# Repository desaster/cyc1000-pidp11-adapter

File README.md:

# pidp11 ↔ cyc1000 adapter

This is an adapter board to connect the
[CYC1000](https://shop.trenz-electronic.de/en/Products/Trenz-Electronic/CYC1000-Intel-Cyclone-10/)
FPGA module to the
[PiDP-11, PDP-11/70 front panel replica](https://obsolescence.wixsite.com/obsolescence/pidp-11).

It is intended to be used with [PDP2011](http://pdp2011.sytse.net/), an FPGA
implementation of the PDP-11 by Sytse van Slooten.

In addition to routing the necessary pins to the panel, the board also
includes some components for use with the PDP2011:

* Micro-SDCard connector
* USB-UART bridge using the [CP2102](https://www.silabs.com/products/interface/usb-bridges/classic-usb-bridges/device.cp2102)
* Pin headers for connecting to [PMODNIC100](https://store.digilentinc.com/pmod-nic100-network-interface-controller/)

## Design considerations

* Power input from PiDP-11 header via VIN
* CYC1000 is placed underneath the adapter for clearance with the back panel
* CP2102 is bus-powered, and will not power the rest of the circuit
* The packages are chosen based on what I happen to have in my shelves

## TODO

* Actually test if the design works
* Replace CP2102 footprint with something easier to solder
* Integrate ENC424J600 to the board

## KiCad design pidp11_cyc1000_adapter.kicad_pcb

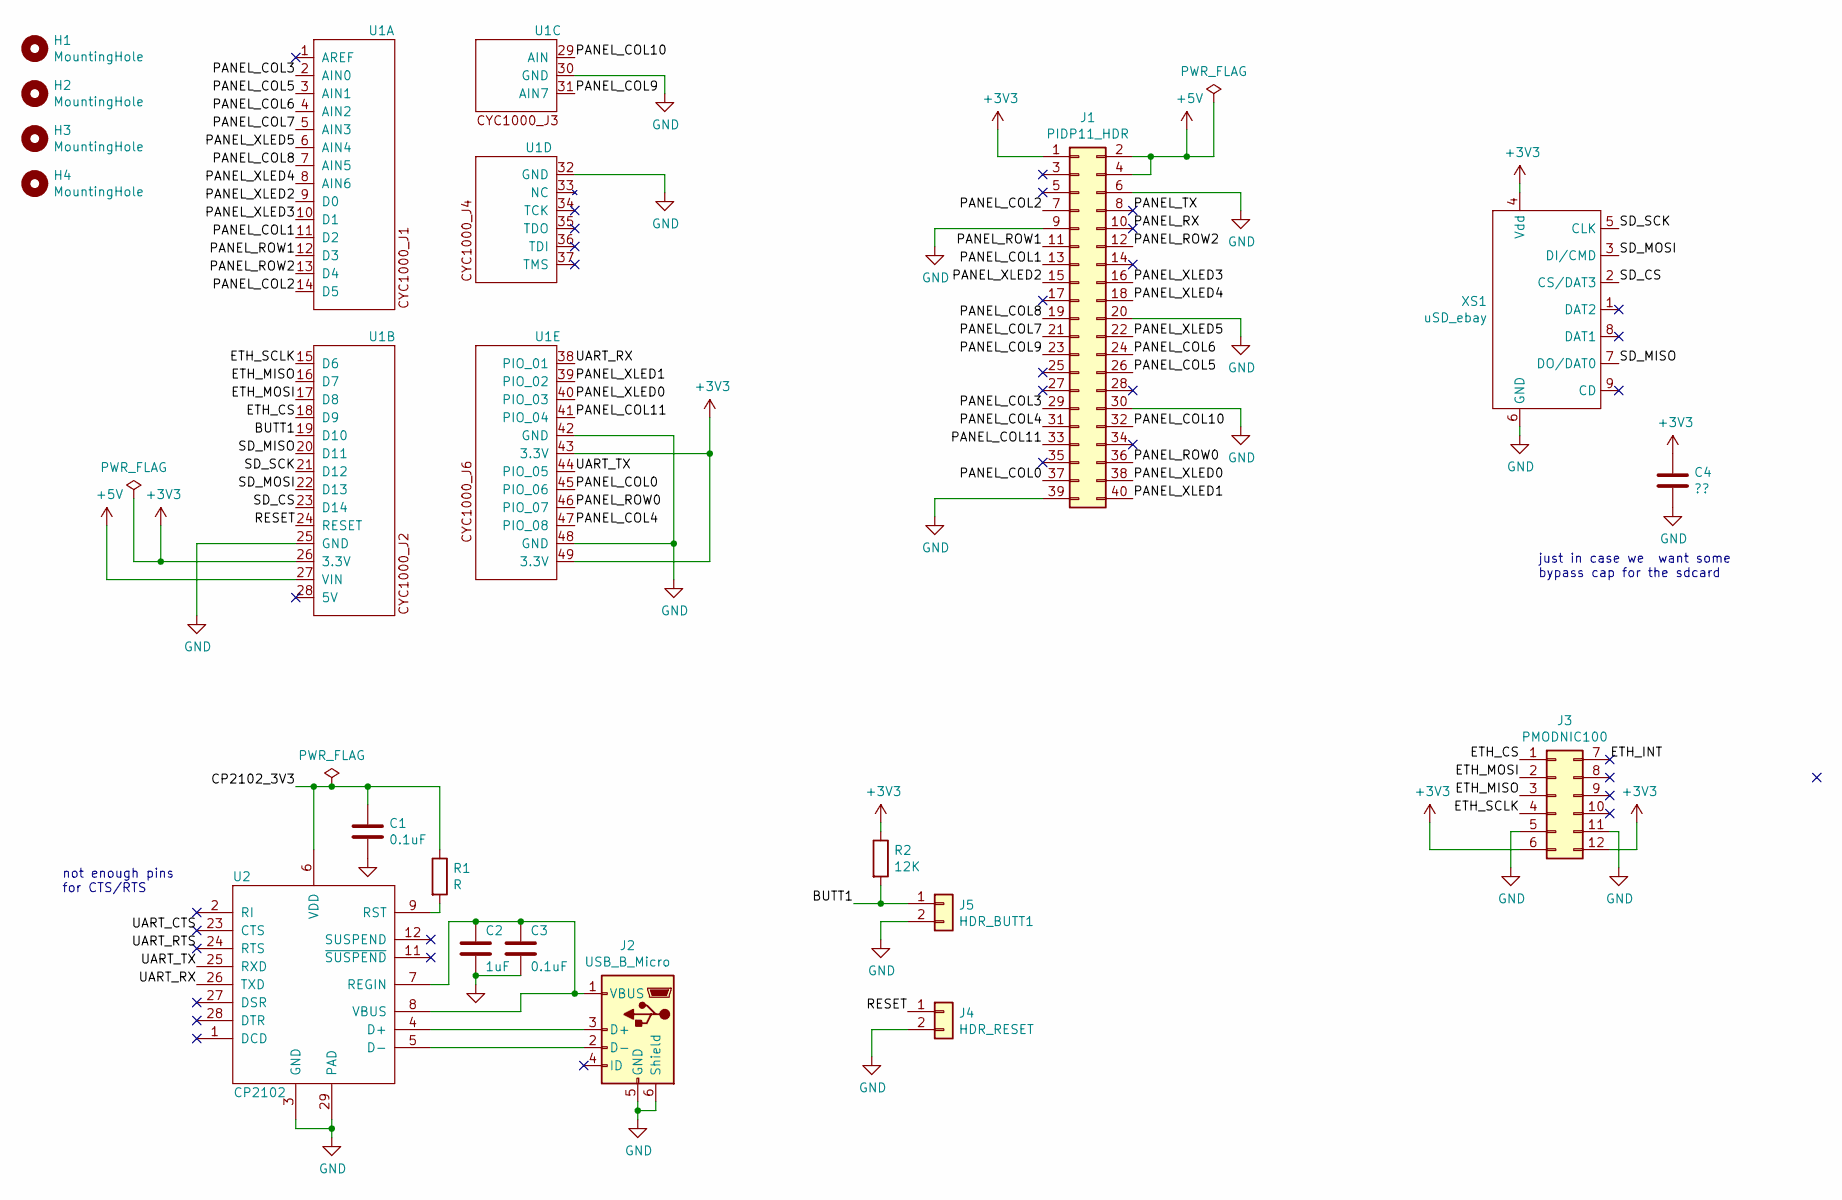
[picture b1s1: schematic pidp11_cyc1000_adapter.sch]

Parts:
C1: 0.1uF; C_0805_2012Metric
C2: 1uF; C_0805_2012Metric_Pad1.15x1.40mm_HandSolder
C3: 0.1uF; C_0805_2012Metric_Pad1.15x1.40mm_HandSolder
C4: ??; C_0805_2012Metric_Pad1.15x1.40mm_HandSolder
H1, H2, H3, H4: MountingHole; MountingHole_RasPI
J1: PIDP11_HDR; PinHeader_2x20_P2.54mm_Vertical
J2: USB_B_Micro; USB_Mini-B_Lumberg_2486_01_Horizontal
J3: PMODNIC100; PMOD_2x06
J4: HDR_RESET; PinHeader_1x02_P2.54mm_Horizontal
J5: HDR_BUTT1; PinHeader_1x02_P2.54mm_Horizontal
R1: R; R_0805_2012Metric_Pad1.15x1.40mm_HandSolder
R2: 12K; R_0805_2012Metric_Pad1.15x1.40mm_HandSolder
U1: CYC1000
U2: CP2102; QFN-28-1EP_5x5mm_Pitch0.5mm
XS1: uSD_ebay; Conn_uSDcard

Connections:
+3V3: C4.1, J1.1, J3.6, J3.12, R2.1, U1.26 (3.3V), U1.43 (3.3V), U1.49 (3.3V), XS1.4 (Vdd)
+5V: J1.2, J1.4, U1.27 (VIN)
/BUTT1: J5.1, R2.2, U1.19 (D10)
/CP2102_3V3: C1.1, R1.1, U2.6 (VDD)
/ETH_CS: J3.1, U1.18 (D9)
/ETH_INT: J3.7
/ETH_MISO: J3.3, U1.16 (D7)
/ETH_MOSI: J3.2, U1.17 (D8)
/ETH_SCLK: J3.4, U1.15 (D6)
/PANEL_COL0: J1.37, U1.45 (PIO_06)
/PANEL_COL1: J1.13, U1.11 (D2)
/PANEL_COL2: J1.7, U1.14 (D5)
/PANEL_COL3: J1.29, U1.2 (AIN0)
/PANEL_COL4: J1.31, U1.47 (PIO_08)
/PANEL_COL5: J1.26, U1.3 (AIN1)
/PANEL_COL6: J1.24, U1.4 (AIN2)
/PANEL_COL7: J1.21, U1.5 (AIN3)
/PANEL_COL8: J1.19, U1.7 (AIN5)
/PANEL_COL9: J1.23, U1.31 (AIN7)
/PANEL_COL10: J1.32, U1.29 (AIN)
/PANEL_COL11: J1.33, U1.41 (PIO_04)
/PANEL_ROW0: J1.36, U1.46 (PIO_07)
/PANEL_ROW1: J1.11, U1.12 (D3)
/PANEL_ROW2: J1.12, U1.13 (D4)
/PANEL_RX: J1.10
/PANEL_TX: J1.8
/PANEL_XLED0: J1.38, U1.40 (PIO_03)
/PANEL_XLED1: J1.40, U1.39 (PIO_02)
/PANEL_XLED2: J1.15, U1.9 (D0)
/PANEL_XLED3: J1.16, U1.10 (D1)
/PANEL_XLED4: J1.18, U1.8 (AIN6)
/PANEL_XLED5: J1.22, U1.6 (AIN4)
/RESET: J4.1, U1.24 (RESET)
/SD_CS: U1.23 (D14), XS1.2 (CS/DAT3)
/SD_MISO: U1.20 (D11), XS1.7 (DO/DAT0)
/SD_MOSI: U1.22 (D13), XS1.3 (DI/CMD)
/SD_SCK: U1.21 (D12), XS1.5 (CLK)
/UART_CTS: U2.23 (CTS)
/UART_RTS: U2.24 (RTS)
/UART_RX: U1.38 (PIO_01), U2.26 (TXD)
/UART_TX: U1.44 (PIO_05), U2.25 (RXD)
GND: C1.2, C2.2, C3.2, C4.2, J1.6, J1.9, J1.20, J1.30, J1.39, J2.5 (GND), J2.6 (Shield), J3.5, J3.11, J4.2, J5.2, U1.25 (GND), U1.30 (GND), U1.32 (GND), U1.42 (GND), U1.48 (GND), U2.3 (GND), U2.29 (PAD), XS1.6 (GND)
unnamed: C2.1, C3.1, J2.1 (VBUS), U2.7 (REGIN), U2.8 (VBUS)
unnamed: J2.2 (D-), U2.5 (D-)
unnamed: J2.3 (D+), U2.4 (D+)
unnamed: R1.2, U2.9 (RST)

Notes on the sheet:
just in case we want some bypass cap for the sdcard
not enough pins for CTS/RTS

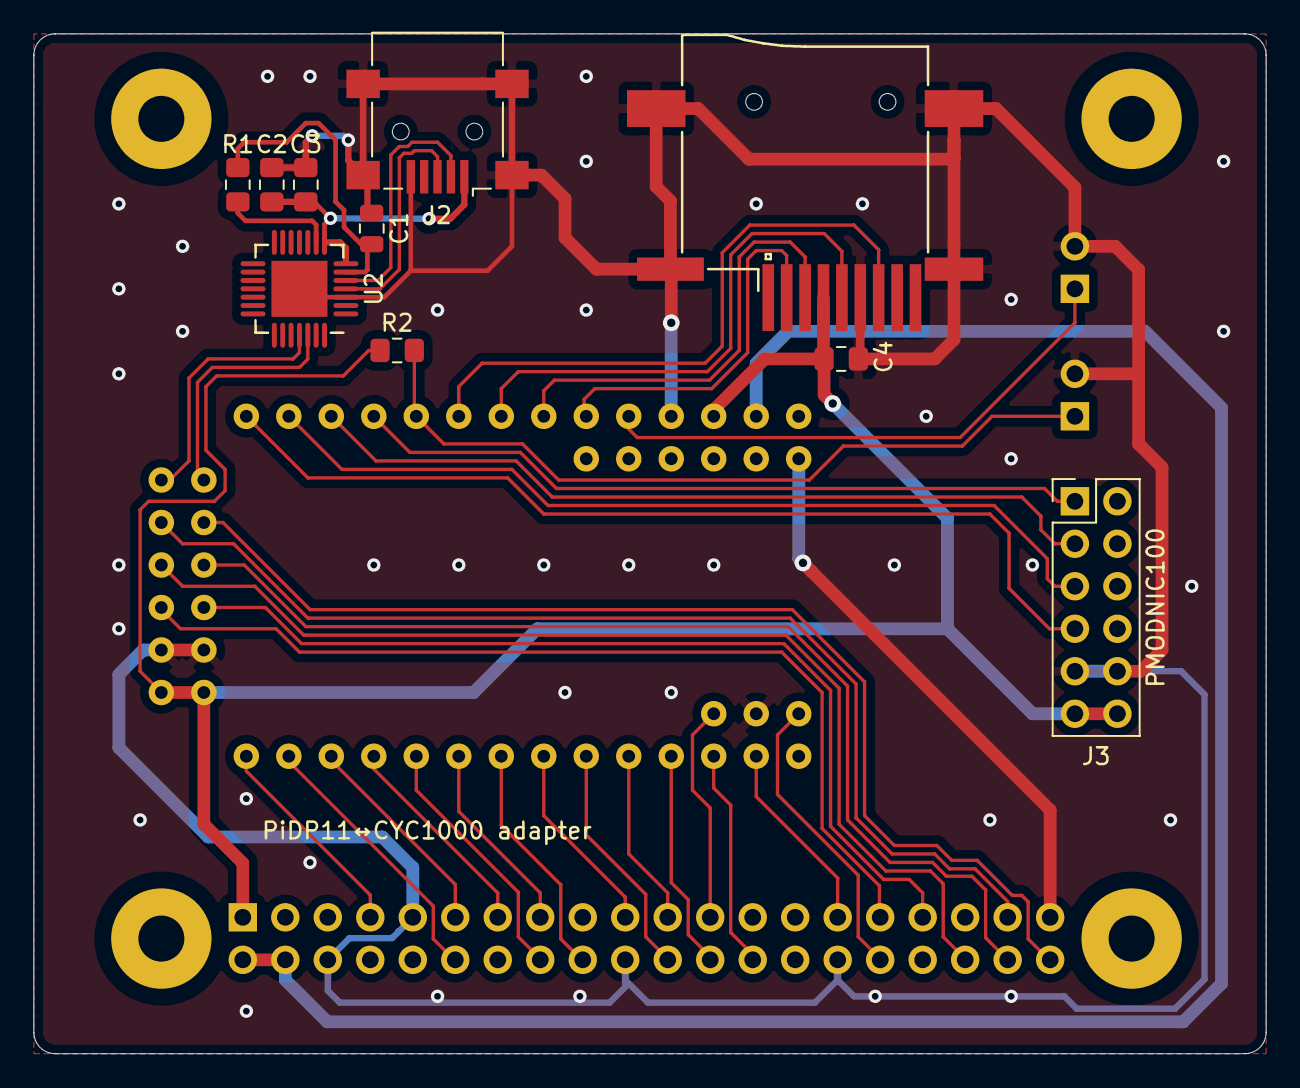
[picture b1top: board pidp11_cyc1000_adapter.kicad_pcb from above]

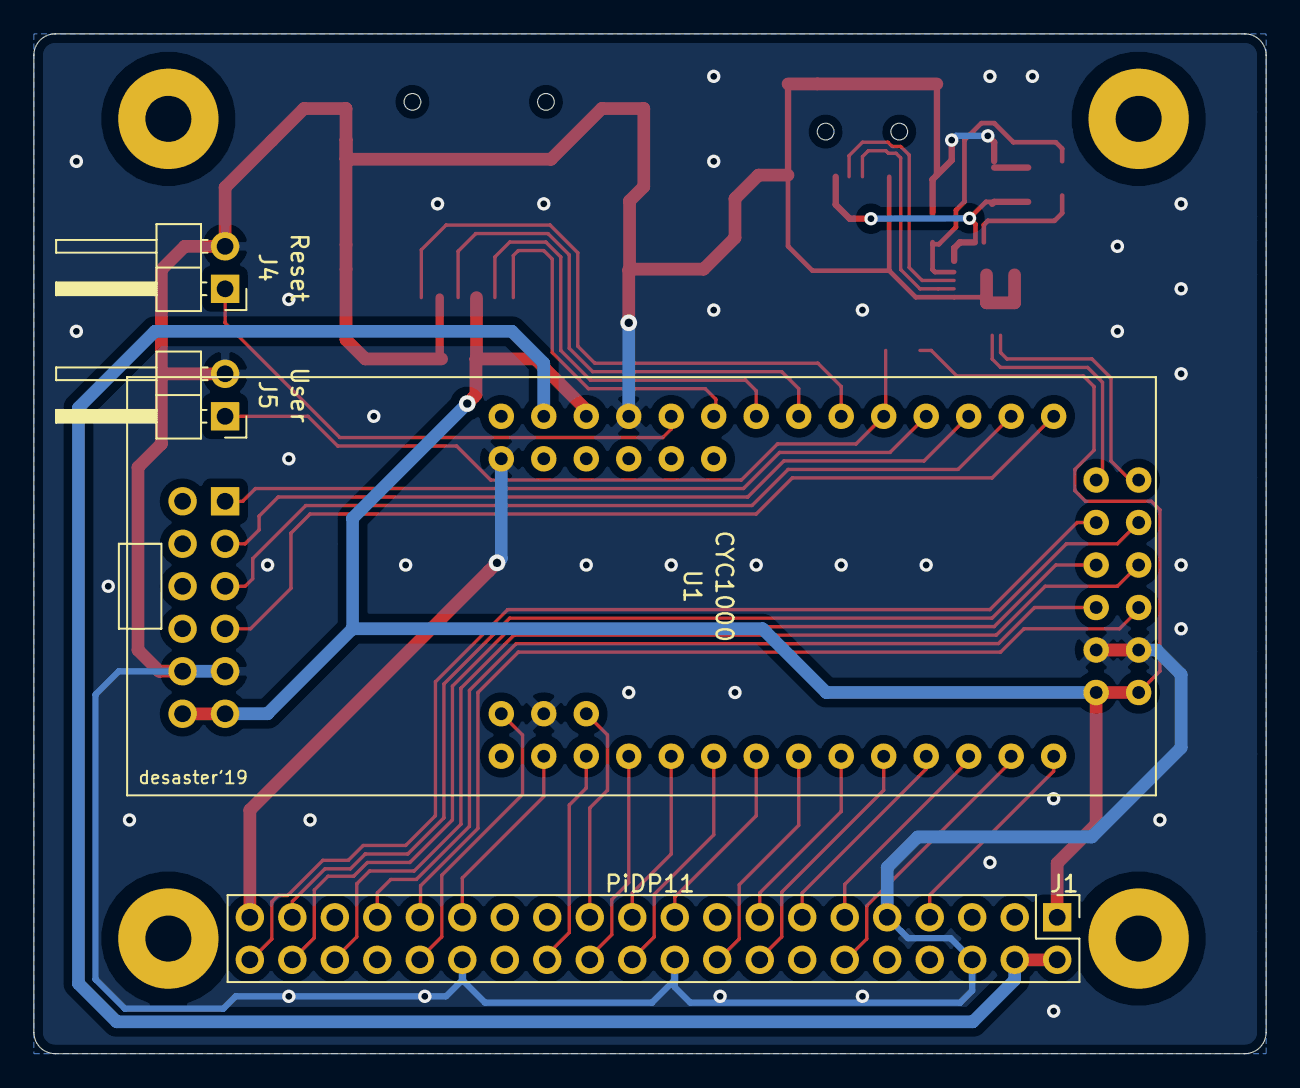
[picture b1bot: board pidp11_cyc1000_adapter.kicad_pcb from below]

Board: 2 copper layers, 73.7 x 61.0 mm, 18 parts (4 on the bottom side), 41 nets.

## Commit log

2019-09-11 symbol and footprint roughly done
2019-11-03 all routed
2019-11-03 add some via stitching
2019-11-05 final tweaks before first test run
2019-11-05 Add README.md
